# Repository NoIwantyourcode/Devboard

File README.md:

# What is this Devboard

This is a custom devboard I have made which uses an RP2040 along with 40 GPIO pins, This also has an inbuild MPU-6500 IMU for all of your tilt and acceleration measuring needs!

# Why I built this

I built this because I was extremely bored on one fine Sunday morning and decided to embark on this project to teach myself about robots and how to design them

# Pictures of the Devboard

  # Schematics - DevBoard

  # PCB board - DevBoard

  # PCB Board - 3D render

  # PCB board assembled and working!

  # Demo!
  Goto <li>https://youtu.be/vsxfW2zVnzc</li>

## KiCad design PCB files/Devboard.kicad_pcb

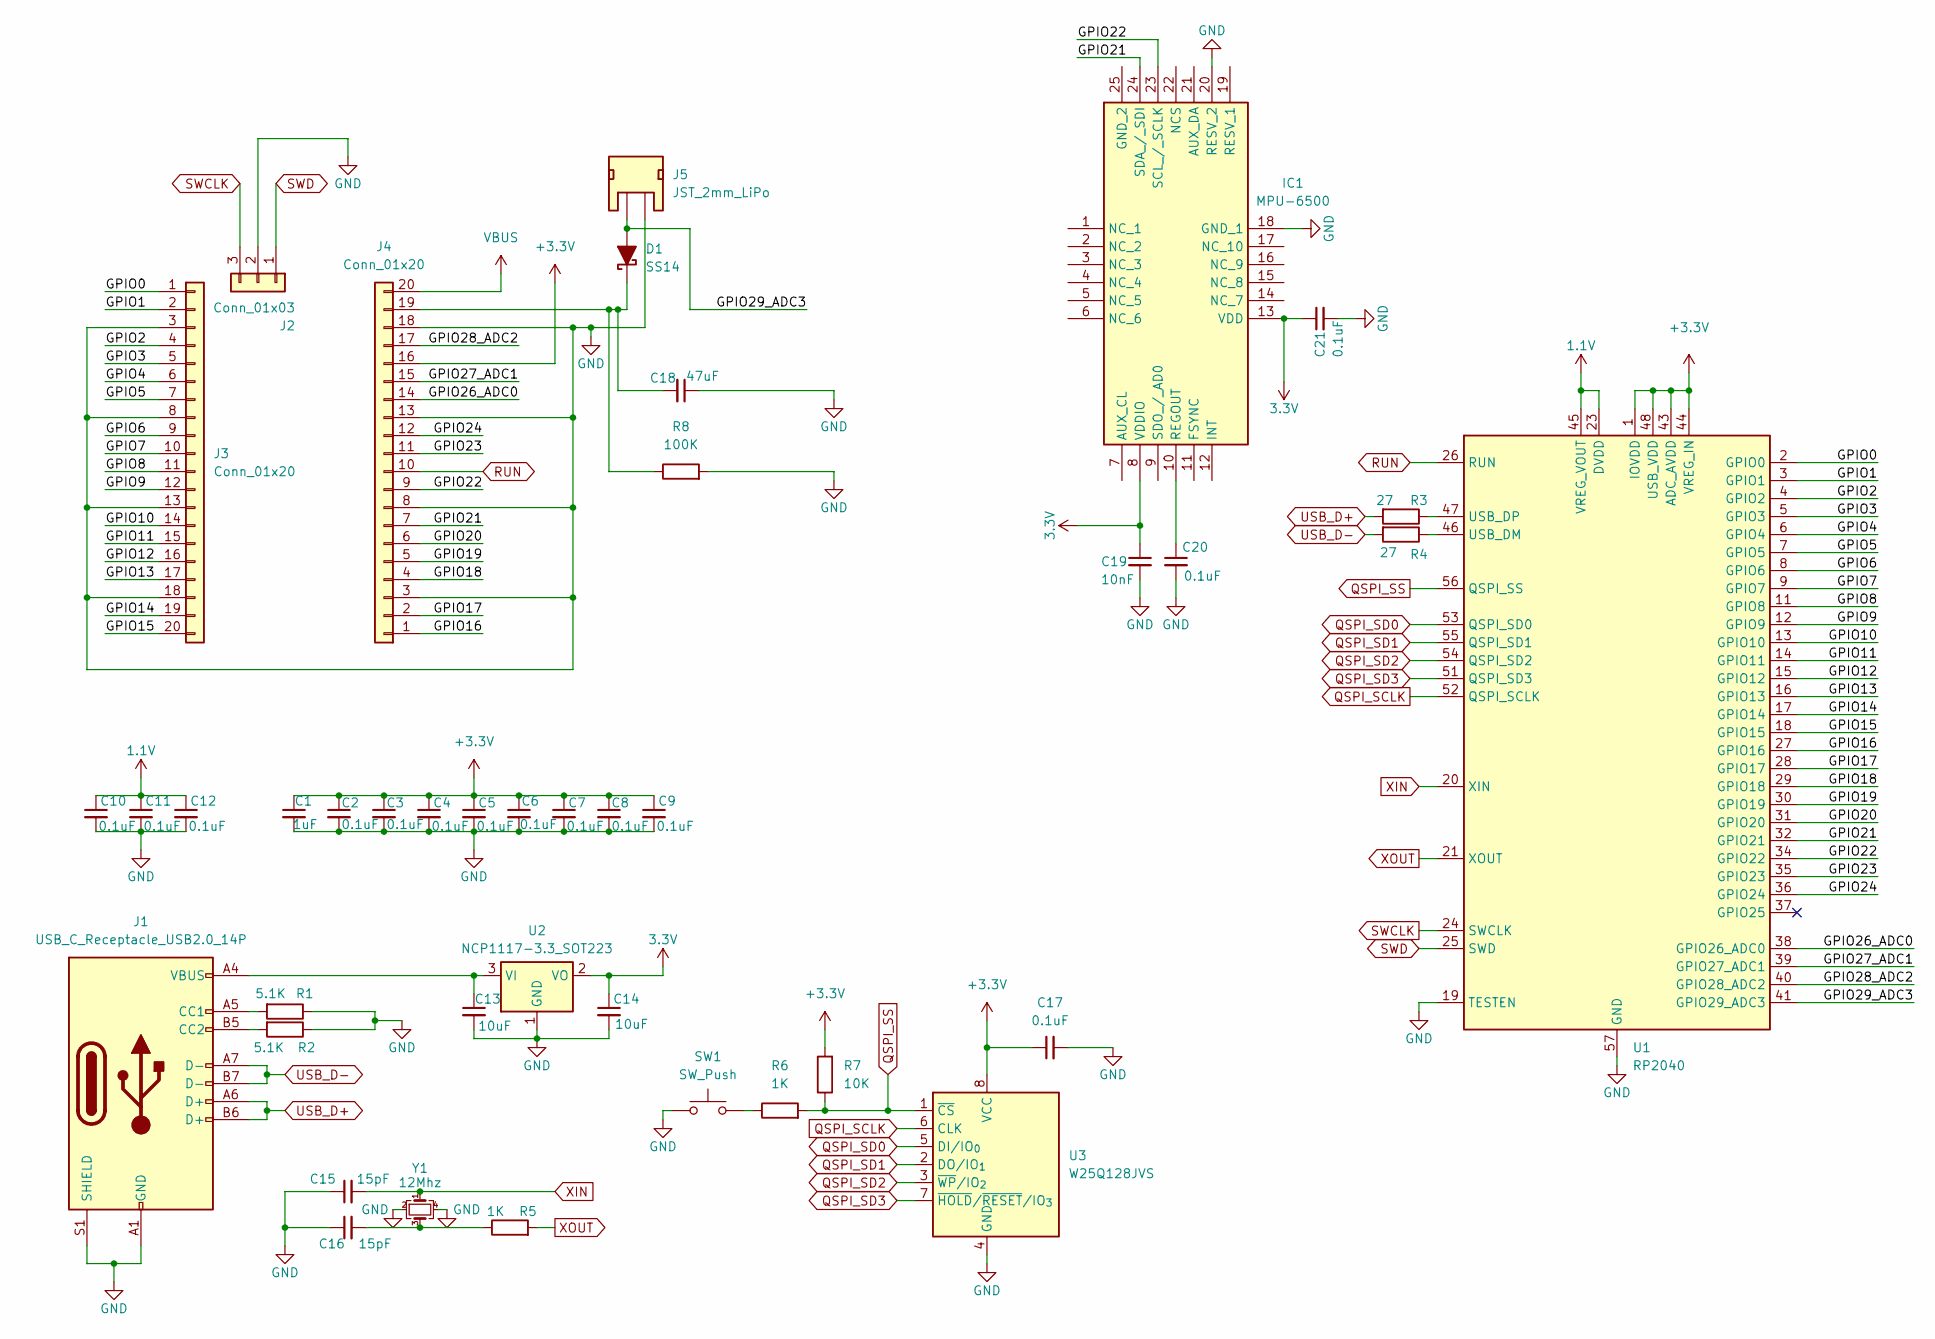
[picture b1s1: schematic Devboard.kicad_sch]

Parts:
C1: 1uF; C_0402_1005Metric_Pad0.74x0.62mm_HandSolder; Voltage 1kV; Tolerance 100%
C2, C3, C4, C5, C6, C7, C8, C9, C10, C11, C12: 0.1uF; C_0402_1005Metric_Pad0.74x0.62mm_HandSolder; Voltage 1kV; Tolerance 100%
C13, C14: 10uF; C_0603_1608Metric_Pad1.08x0.95mm_HandSolder; Voltage 1kV; Tolerance 100%
C15, C16: 15pF; C_0402_1005Metric; Voltage 50V; Tolerance 5%
C17: 0.1uF; C_0402_1005Metric; Voltage 16V; Tolerance 10%
C18: 47uF; C_0603_1608Metric; Voltage 1kV; Tolerance 100%
C19: 10nF; C_0603_1608Metric; Voltage 1kV; Tolerance 100%
C20, C21: 0.1uF; C_0603_1608Metric; Voltage 1kV; Tolerance 100%
D1: SS14; D_SMA
IC1: MPU-6500; QFN40P300X300X95-25N-D; Manufacturer_Part_Number MPU-6500; Mouser Part Number 410-MPU-6500
J1: USB_C_Receptacle_USB2.0_14P; USB_C_Receptacle_HRO_TYPE-C-31-M-12
J2: Conn_01x03; PinHeader_1x03_P2.54mm_Vertical
J3, J4: Conn_01x20; PinHeader_1x20_P2.54mm_Vertical
J5: JST_2mm_LiPo; JST_XA_S02B-XASK-1N-BN_1x02_P2.50mm_Horizontal
R1, R2: 5.1K; R_0402_1005Metric_Pad0.72x0.64mm_HandSolder
R3, R4: 27; R_0402_1005Metric_Pad0.72x0.64mm_HandSolder
R5, R6: 1K; R_0402_1005Metric_Pad0.72x0.64mm_HandSolder
R7: 10K; R_0402_1005Metric_Pad0.72x0.64mm_HandSolder
R8: 100K; C_0603_1608Metric_Pad1.08x0.95mm_HandSolder
SW1: SW_Push; SW_Push_SPST_NO_Alps_SKRK
U1: RP2040; QFN-56-1EP_7x7mm_P0.4mm_EP3.2x3.2mm
U2: NCP1117-3.3_SOT223; SOT-223-3_TabPin2
U3: W25Q128JVS; SOIC-8_5.3x5.3mm_P1.27mm
Y1: 12Mhz; Crystal_SMD_3225-4Pin_3.2x2.5mm

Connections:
1.1V: C10.1, C11.1, C12.1, U1.23 (DVDD), U1.45 (VREG_VOUT), U1.50 (DVDD)
3.3V: C14.1, C19.1, C21.1, IC1.8 (VDDIO), IC1.13 (VDD), U2.2 (VO)
+3.3V: C1.1, C2.1, C3.1, C4.1, C5.1, C6.1, C7.1, C8.1, C9.1, C17.1, J4.16, R7.2, U1.1 (IOVDD), U1.10 (IOVDD), U1.22 (IOVDD), U1.33 (IOVDD), U1.42 (IOVDD), U1.43 (ADC_AVDD), U1.44 (VREG_IN), U1.48 (USB_VDD), U1.49 (IOVDD), U3.8 (VCC)
/GPIO0: J3.1, U1.2 (GPIO0)
/GPIO1: J3.2, U1.3 (GPIO1)
/GPIO2: J3.4, U1.4 (GPIO2)
/GPIO3: J3.5, U1.5 (GPIO3)
/GPIO4: J3.6, U1.6 (GPIO4)
/GPIO5: J3.7, U1.7 (GPIO5)
/GPIO6: J3.9, U1.8 (GPIO6)
/GPIO7: J3.10, U1.9 (GPIO7)
/GPIO8: J3.11, U1.11 (GPIO8)
/GPIO9: J3.12, U1.12 (GPIO9)
/GPIO10: J3.14, U1.13 (GPIO10)
/GPIO11: J3.15, U1.14 (GPIO11)
/GPIO12: J3.16, U1.15 (GPIO12)
/GPIO13: J3.17, U1.16 (GPIO13)
/GPIO14: J3.19, U1.17 (GPIO14)
/GPIO15: J3.20, U1.18 (GPIO15)
/GPIO16: J4.1, U1.27 (GPIO16)
/GPIO17: J4.2, U1.28 (GPIO17)
/GPIO18: J4.4, U1.29 (GPIO18)
/GPIO19: J4.5, U1.30 (GPIO19)
/GPIO20: J4.6, U1.31 (GPIO20)
/GPIO21: IC1.24 (SDA_/_SDI), J4.7, U1.32 (GPIO21)
/GPIO22: IC1.23 (SCL_/_SCLK), J4.9, U1.34 (GPIO22)
/GPIO23: J4.11, U1.35 (GPIO23)
/GPIO24: J4.12, U1.36 (GPIO24)
/GPIO26_ADC0: J4.14, U1.38 (GPIO26_ADC0)
/GPIO27_ADC1: J4.15, U1.39 (GPIO27_ADC1)
/GPIO28_ADC2: J4.17, U1.40 (GPIO28_ADC2)
/GPIO29_ADC3: D1.2 (A), J5.2 (+), U1.41 (GPIO29_ADC3)
GND: C1.2, C2.2, C3.2, C4.2, C5.2, C6.2, C7.2, C8.2, C9.2, C10.2, C11.2, C12.2, C13.2, C14.2, C15.1, C16.1, C17.2, C18.1, C19.2, C20.2, C21.2, IC1.18 (GND_1), IC1.20 (RESV_2), J1.A1 (GND), J1.A12 (GND), J1.B1 (GND), J1.B12 (GND), J1.S1 (SHIELD), J2.2, J3.3, J3.8, J3.13, J3.18, J4.3, J4.8, J4.13, J4.18, J5.1 (-), R1.1, R2.1, R8.2, SW1.1, U1.19 (TESTEN), U1.57 (GND), U2.1 (GND), U3.4 (GND), Y1.2, Y1.4
unnamed: C16.2, R5.1, Y1.3
unnamed: C18.2, D1.1 (K), J4.19, R8.1
unnamed: C20.1, IC1.10 (REGOUT)
unnamed: J1.A5 (CC1), R1.2
unnamed: J1.B5 (CC2), R2.2
unnamed: R6.1, SW1.2
unnamed: R4.1, U1.46 (USB_DM)
unnamed: R3.1, U1.47 (USB_DP)
unnamed: C13.1, J1.A4 (VBUS), J1.A9 (VBUS), J1.B4 (VBUS), J1.B9 (VBUS), U2.3 (VI)
QSPI_SCLK: U1.52 (QSPI_SCLK), U3.6 (CLK)
QSPI_SD0: U1.53 (QSPI_SD0), U3.5 (DI/IO_{0})
QSPI_SD1: U1.55 (QSPI_SD1), U3.2 (DO/IO_{1})
QSPI_SD2: U1.54 (QSPI_SD2), U3.3 (~WP/IO_{2})
QSPI_SD3: U1.51 (QSPI_SD3), U3.7 (~HOLD/~RESET/IO_{3})
QSPI_SS: R6.2, R7.1, U1.56 (QSPI_SS), U3.1 (~CS)
RUN: J4.10, U1.26 (RUN)
SWCLK: J2.3, U1.24 (SWCLK)
SWD: J2.1, U1.25 (SWD)
USB_D+: J1.A6 (D+), J1.B6 (D+), R3.2
USB_D-: J1.A7 (D-), J1.B7 (D-), R4.2
VBUS: J4.20
XIN: C15.2, U1.20 (XIN), Y1.1
XOUT: R5.2, U1.21 (XOUT)

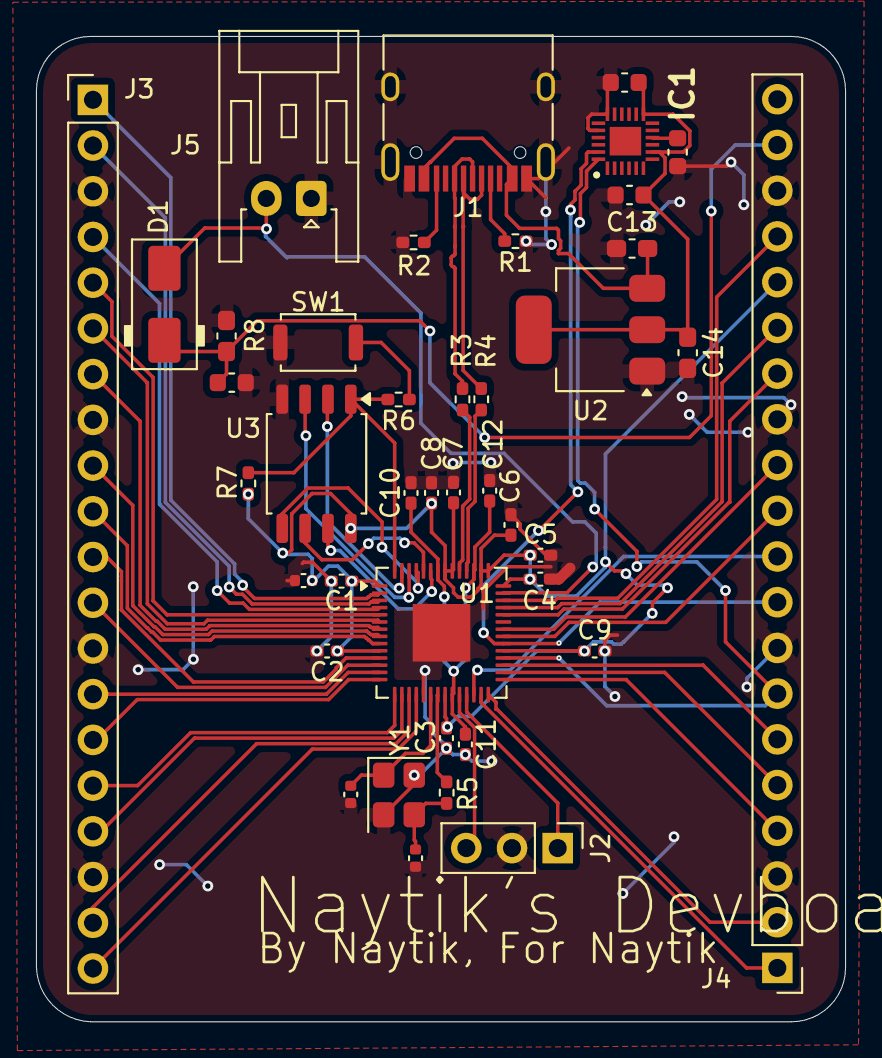
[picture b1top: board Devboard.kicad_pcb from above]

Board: 2 copper layers, 44.9 x 54.7 mm, 41 parts (0 on the bottom side), 55 nets.

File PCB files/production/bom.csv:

Designator,Footprint,Quantity,Value,LCSC Part #
C1,0402,1,1uF,
"C10, C11, C12, C17, C2, C3, C4, C5, C6, C7, C8, C9",0402,12,0.1uF,
"C13, C14",0603,2,10uF,
"C15, C16",0402,2,15pF,
C18,0603,1,47uF,
C19,0603,1,10nF,
"C20, C21",0603,2,0.1uF,
D1,D_SMA,1,SS14,
IC1,QFN40P300X300X95-25N-D,1,MPU-6500,
J1,USB_C_Receptacle_HRO_TYPE-C-31-M-12,1,USB_C_Receptacle_USB2.0_14P,
J2,PinHeader_1x03_P2.54mm_Vertical,1,Conn_01x03,
"J3, J4",PinHeader_1x20_P2.54mm_Vertical,2,Conn_01x20,
J5,JST_XA_S02B-XASK-1N-BN_1x02_P2.50mm_Horizontal,1,JST_2mm_LiPo,
"R1, R2",0402,2,5.1K,
"R3, R4",0402,2,27,
"R5, R6",0402,2,1K,
R7,0402,1,10K,
R8,0603,1,100K,
SW1,SW_Push_SPST_NO_Alps_SKRK,1,SW_Push,
U1,QFN-56-1EP_7x7mm_P0.4mm_EP3.2x3.2mm,1,RP2040,
U2,SOT-223-3_TabPin2,1,NCP1117-3.3_SOT223,
U3,SOIC-8_5.3x5.3mm_P1.27mm,1,W25Q128JVS,
Y1,Crystal_SMD_3225-4Pin_3.2x2.5mm,1,12Mhz,

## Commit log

2026-05-19 Add README for RP2040 devboard project
    Added introductory information and images for the RP2040 devboard project.
2026-05-19 Added an IMU, Solved all DRC thermal relief errors + routed IMU
2026-05-19 Changed IMU from MPU-6500 to ICM-20948
2026-05-20 Updated Devboard
2026-05-20 Re-routed the board to a 2-layer PCB and removed IMU unit
2026-05-20 Add schematics and PCB board images to README
2026-05-21 organisation
2026-05-21 added MPU-6500 IMU
2026-05-21 removed old production file, new one is in the PCB files folder
2026-05-21 Added extra dimensions
2026-05-21 added bom
2026-05-21 smth
    Not very sure...
2026-05-22 added rounded corners and also added silkscreen text
2026-05-23 changes for rounded corners!
2026-05-23 updated for rounded corners
2026-06-02 I added a tic tac toe board to the back
2026-06-02 added better art
2026-06-02 some random files
2026-06-03 added better silkscreen art
2026-06-03 added better images
2026-06-08 something
2026-06-29 Update JOURNAL.md with new entry and total time
    Updated total time and added entry for June 18th detailing assembly and troubleshooting of the devboard.
2026-06-29 Update total time in JOURNAL.md
    Updated total time spent on project from 11.5 to 12 hours.
